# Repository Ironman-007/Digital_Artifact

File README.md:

# Digital_Artifact

Input devices:
- mouse encoder: https://www.amazon.com/gp/product/B0CF9FS3QS/ref=ppx_yo_dt_b_asin_title_o00_s00?ie=UTF8&psc=1
- thumb joystick: https://www.adafruit.com/product/5628
- thumbwheel:
  - https://www.mouser.com/ProductDetail/688-SLLB510100
  - https://www.digikey.com/en/products/detail/alps-alpine/RK10J11R0A0L/21721634?_gl=1*ibrmm*_up*MQ..&gclid=CjwKCAjwvIWzBhAlEiwAHHWgvW0KJP7YJKtc8Nkp65_yvyd6hXw_fZWHygCL2rq1JPE7rxjxQ-IDzBoCs5MQAvD_BwE
- switch: https://www.amazon.com/TWTADE-Momentary-Assortment-Latching-QC-6X6MM/dp/B0858XRGYW/ref=sr_1_1_sspa?crid=2G949J8CR9FFL&dib=eyJ2IjoiMSJ9.kLP3myFYEu7YxaxVJFxt0CR7cWAJtdNJurHc0SBF_I0Rnps__aZ0KqfE4xTtx1MC42MvBkPqKHbfML0_veETEkCh2VtVrYn88wwgkNA-9Elocw1Sk3cp6kjohcve9LoceMxmj3VmeW1gmaoNqY4txQSBajDX9QftLhwdBde_QJkDxFte7JVvVia5f__PGqh0Lh0pOEfo_RKa8_AL1vu4oqmdkYQ97DKHsVdOGzsnvqA.uAgLgaC6A2uq8BuUuJIR0Q7ERczKVlZagGLPBY-yLbA&dib_tag=se&keywords=tactile+switch&qid=1717622919&sprefix=tactile+switch%2Caps%2C122&sr=8-1-spons&sp_csd=d2lkZ2V0TmFtZT1zcF9hdGY&psc=1

MCU:
BC832

IMU:
ICM-20948 (9-DoF)

Actuator:
Linear vibrator

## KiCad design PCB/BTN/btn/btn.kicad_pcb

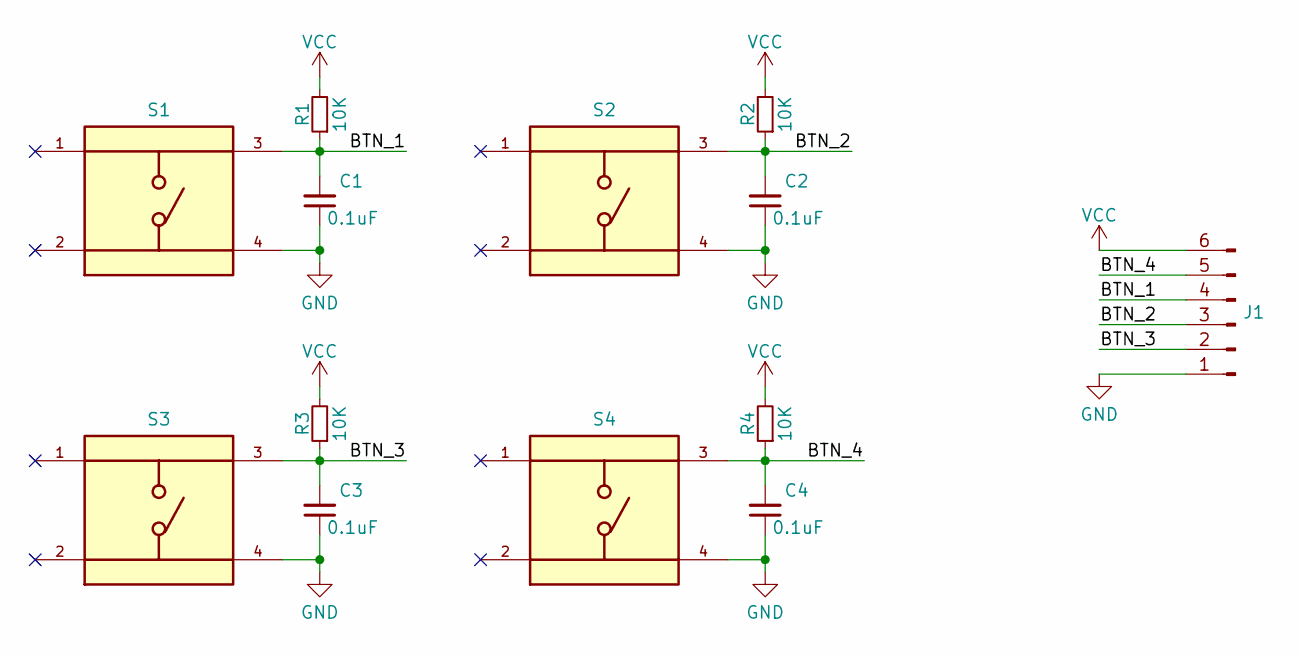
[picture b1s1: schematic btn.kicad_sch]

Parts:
C1, C2, C3, C4: 0.1uF; C_0402_1005Metric_Pad0.74x0.62mm_HandSolder
J1: Conn_01x06_Pin; Pinheader_2mmx6
R1, R2, R3, R4: 10K; R_0402_1005Metric_Pad0.72x0.64mm_HandSolder
S1, S2, S3, S4: TS04-66-95-BK-100-SMT; SW_TS04-66-95-BK-100-SMT; PARTREV 1.0

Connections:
/BTN_1: C1.2, J1.4, R1.1, S1.3
/BTN_2: C2.2, J1.3, R2.1, S2.3
/BTN_3: C3.2, J1.2, R3.1, S3.3
/BTN_4: C4.2, J1.5, R4.1, S4.3
GND: C1.1, C2.1, C3.1, C4.1, J1.1, S1.4, S2.4, S3.4, S4.4
VCC: J1.6, R1.2, R2.2, R3.2, R4.2

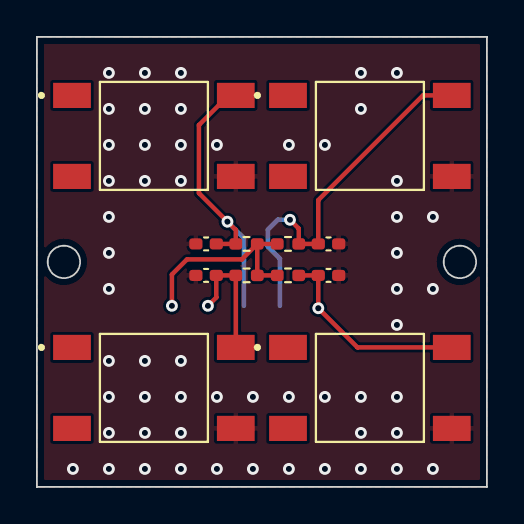
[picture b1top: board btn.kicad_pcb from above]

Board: 2 copper layers, 25.0 x 25.0 mm, 13 parts (1 on the bottom side), 6 nets.

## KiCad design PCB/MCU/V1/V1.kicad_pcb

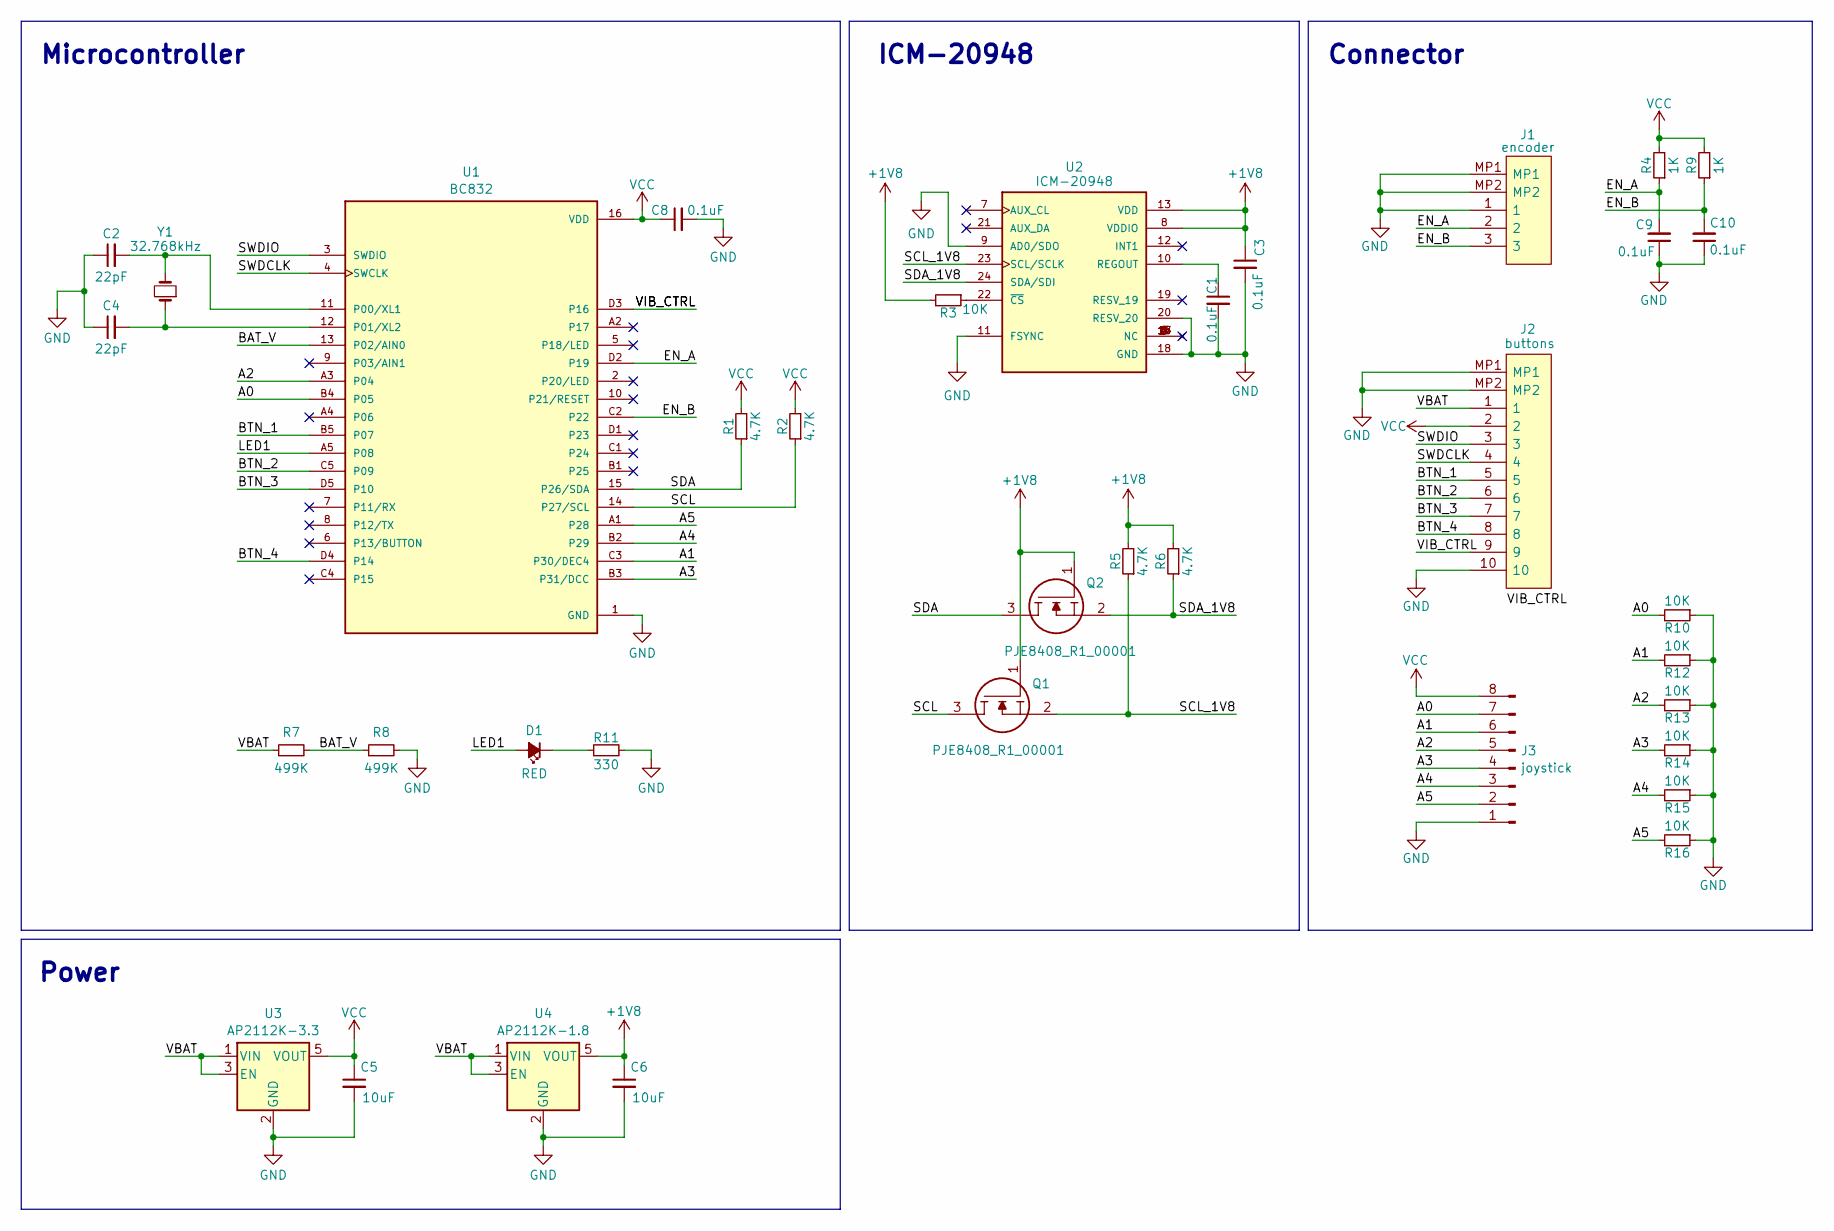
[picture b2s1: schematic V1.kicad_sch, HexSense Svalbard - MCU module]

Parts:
C1, C3, C8, C9, C10: 0.1uF; C_0402_1005Metric_Pad0.74x0.62mm_HandSolder
C2, C4: 22pF; C_0402_1005Metric_Pad0.74x0.62mm_HandSolder
C5, C6: 10uF; C_0402_1005Metric_Pad0.74x0.62mm_HandSolder
D1: RED; LED_0603_1608Metric_Pad1.05x0.95mm_HandSolder
J1: encoder; BM03BSRSSTBTLFSN; Manufacturer_Part_Number BM03B-SRSS-TBT(LF)(SN); Mouser Part Number N/A
J2: buttons; BM10BSRSSTBLFSN; Manufacturer_Part_Number BM10B-SRSS-TB (LF)(SN)
J3: joystick; pinheader_pitch_2mmx8
Q1, Q2: PJE8408_R1_00001; SOTFL50P160X60-3N; Manufacturer_Part_Number PJE8408_R1_00001; Mouser Part Number 241-PJE8408_R1_00001
R1, R2, R5, R6: 4.7K; R_0402_1005Metric_Pad0.72x0.64mm_HandSolder
R3, R10, R12, R13, R14, R15, R16: 10K; R_0402_1005Metric_Pad0.72x0.64mm_HandSolder
R4, R9: 1K; R_0402_1005Metric_Pad0.72x0.64mm_HandSolder
R7, R8: 499K; R_0402_1005Metric_Pad0.72x0.64mm_HandSolder
R11: 330; R_0402_1005Metric_Pad0.72x0.64mm_HandSolder
U1: BC832; XCVR_BC832
U2: ICM-20948; InvenSense_QFN-24_3x3mm_P0.4mm; PARTREV 1.3
U3: AP2112K-3.3; SOT-23-5
U4: AP2112K-1.8; SOT-23-5
Y1: 32.768kHz; C_0805_2012Metric_Pad1.18x1.45mm_HandSolder

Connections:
+1V8: C3.1, C6.1, Q1.1, Q2.1, R3.2, R5.2, R6.2, U2.8 (VDDIO), U2.13 (VDD), U4.5 (VOUT)
/A0: J3.7, R10.2, U1.B4 (P05)
/A1: J3.6, R12.2, U1.C3 (P30/DEC4)
/A2: J3.5, R13.2, U1.A3 (P04)
/A3: J3.4, R14.2, U1.B3 (P31/DCC)
/A4: J3.3, R15.2, U1.B2 (P29)
/A5: J3.2, R16.2, U1.A1 (P28)
/BAT_V: R7.2, R8.1, U1.13 (P02/AIN0)
/BTN_1: J2.5, U1.B5 (P07)
/BTN_2: J2.6, U1.C5 (P09)
/BTN_3: J2.7, U1.D5 (P10)
/BTN_4: J2.8, U1.D4 (P14)
/EN_A: C9.2, J1.2, R4.1, U1.D2 (P19)
/EN_B: C10.2, J1.3, R9.1, U1.C2 (P22)
/LED1: D1.2 (A), U1.A5 (P08)
/SCL: Q1.3, R2.1, U1.14 (P27/SCL)
/SCL_1V8: Q1.2, R5.1, U2.23 (SCL/SCLK)
/SDA: Q2.3, R1.1, U1.15 (P26/SDA)
/SDA_1V8: Q2.2, R6.1, U2.24 (SDA/SDI)
/SWDCLK: J2.4, U1.4 (SWCLK)
/SWDIO: J2.3, U1.3 (SWDIO)
/VBAT: J2.1, R7.1, U3.1 (VIN), U3.3 (EN), U4.1 (VIN), U4.3 (EN)
/VIB_CTRL: J2.9, U1.D3 (P16)
GND: C1.2, C2.1, C3.2, C4.1, C5.2, C6.2, C8.2, C9.1, C10.1, J1.1, J1.MP1, J1.MP2, J2.10, J2.MP1, J2.MP2, J3.1, R8.2, R10.1, R11.2, R12.1, R13.1, R14.1, R15.1, R16.1, U1.1 (GND), U2.9 (AD0/SDO), U2.11 (FSYNC), U2.18 (GND), U2.20 (RESV_20), U3.2 (GND), U4.2 (GND)
unnamed: D1.1 (K), R11.1
unnamed: C2.2, U1.11 (P00/XL1), Y1.2
unnamed: C4.2, U1.12 (P01/XL2), Y1.1
unnamed: C1.1, U2.10 (REGOUT)
unnamed: R3.1, U2.22 (~CS)
VCC: C5.1, C8.1, J2.2, J3.8, R1.2, R2.2, R4.2, R9.2, U1.16 (VDD), U3.5 (VOUT)

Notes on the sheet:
Microcontroller
ICM-20948
Power
Connector

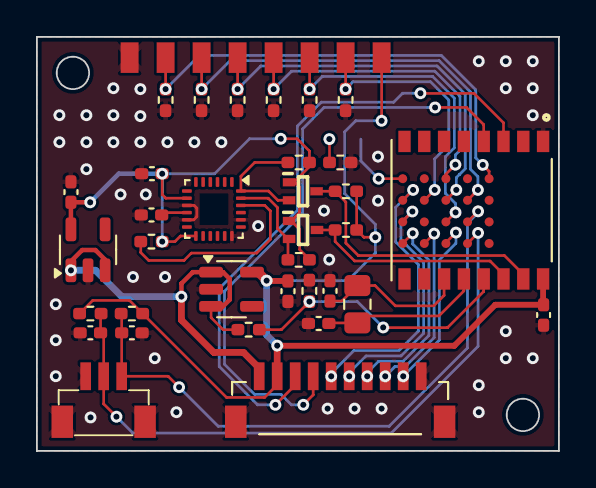
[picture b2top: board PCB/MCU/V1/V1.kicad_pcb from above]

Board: 2 copper layers, 29.0 x 23.0 mm, 36 parts (1 on the bottom side), 30 nets.

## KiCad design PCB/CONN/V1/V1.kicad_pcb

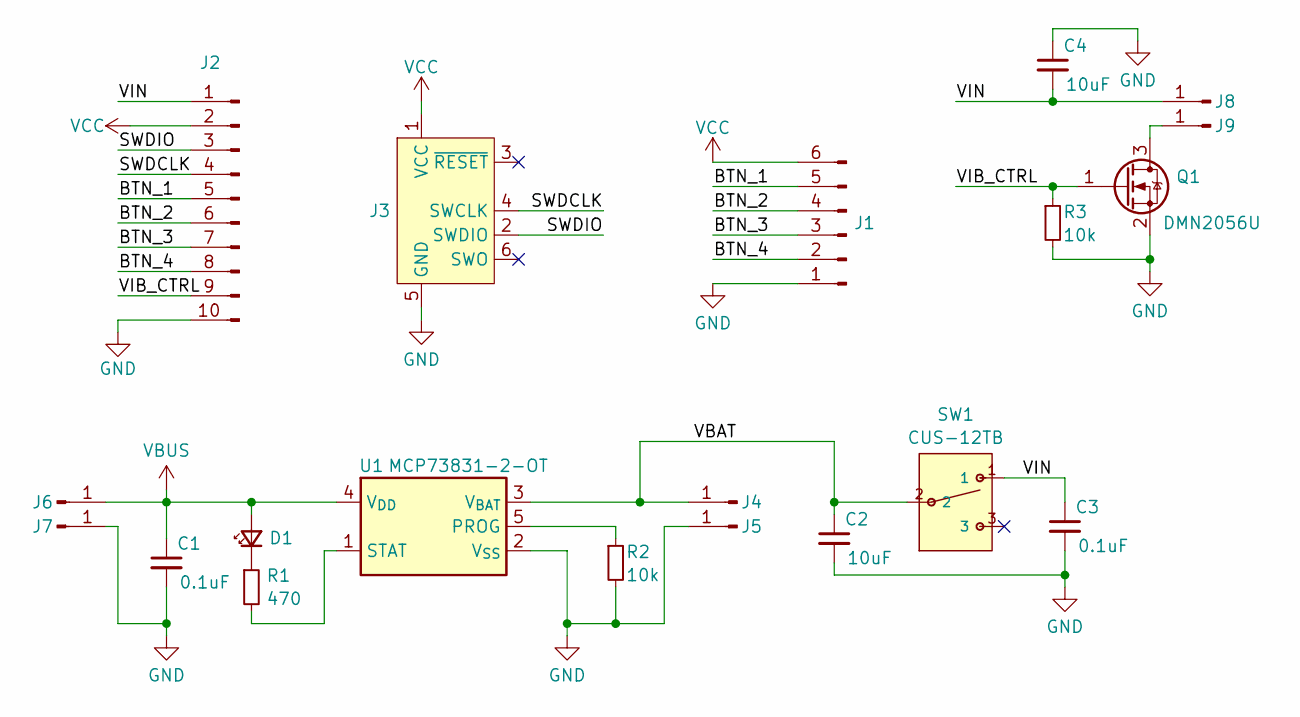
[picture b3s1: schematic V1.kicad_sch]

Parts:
C1, C3: 0.1uF; C_0402_1005Metric_Pad0.74x0.62mm_HandSolder
C2, C4: 10uF; C_0805_2012Metric_Pad1.18x1.45mm_HandSolder
D1: LED_Small; LED_0603_1608Metric_Pad1.05x0.95mm_HandSolder
J1: Conn_01x06_Pin; Pinheader_2mmx6
J2: Conn_01x10_Pin; Pinheader_2mmx10
J3: Conn_ARM_SWD_TagConnect_TC2030-NL; Tag-Connect_TC2030-IDC-NL_2x03_P1.27mm_Vertical
J4, J5, J6, J7, J8, J9: Conn_01x01_Pin; 1_pin
Q1: DMN2056U; SOT-23
R1: 470; R_0402_1005Metric_Pad0.72x0.64mm_HandSolder
R2, R3: 10k; R_0402_1005Metric_Pad0.72x0.64mm_HandSolder
SW1: CUS-12TB; CUS-12B; MANUFACTURER_PART_NUMBER CUS-12TB
U1: MCP73831-2-OT; SOT-23-5

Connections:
/BTN_1: J1.5, J2.5
/BTN_2: J1.4, J2.6
/BTN_3: J1.3, J2.7
/BTN_4: J1.2, J2.8
/SWDCLK: J2.4, J3.4 (SWCLK)
/SWDIO: J2.3, J3.2 (SWDIO)
/VBAT: C2.1, J4.1, SW1.2, U1.3 (V_{BAT})
/VIB_CTRL: J2.9, Q1.1 (G), R3.1
/VIN: C3.1, C4.2, J2.1, J8.1, SW1.1
GND: C1.2, C2.2, C3.2, C4.1, J1.1, J2.10, J3.5 (GND), J5.1, J7.1, Q1.2 (S), R2.2, R3.2, U1.2 (V_{SS})
unnamed: D1.1 (K), R1.1
unnamed: J9.1, Q1.3 (D)
unnamed: R2.1, U1.5 (PROG)
unnamed: R1.2, U1.1 (STAT)
VBUS: C1.1, D1.2 (A), J6.1, U1.4 (V_{DD})
VCC: J1.6, J2.2, J3.1 (VCC)

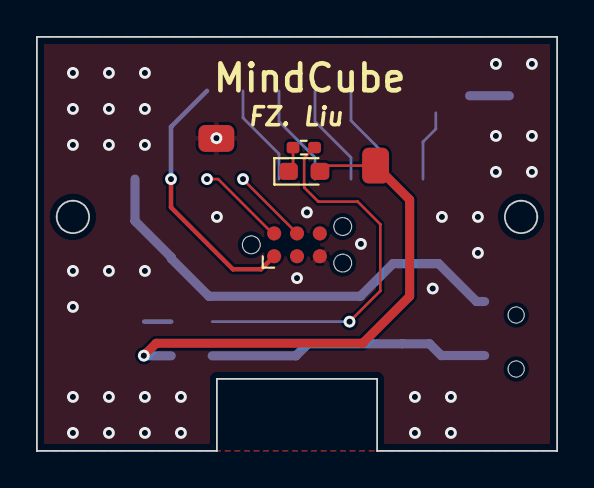
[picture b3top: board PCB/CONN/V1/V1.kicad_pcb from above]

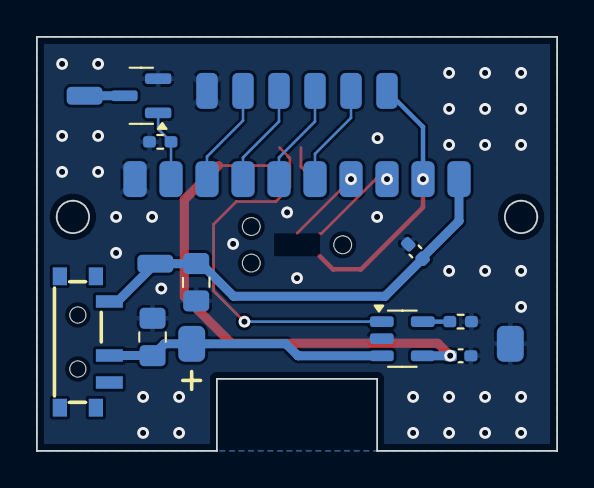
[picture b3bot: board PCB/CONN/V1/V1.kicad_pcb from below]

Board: 2 copper layers, 28.9 x 23.0 mm, 20 parts (15 on the bottom side), 16 nets.

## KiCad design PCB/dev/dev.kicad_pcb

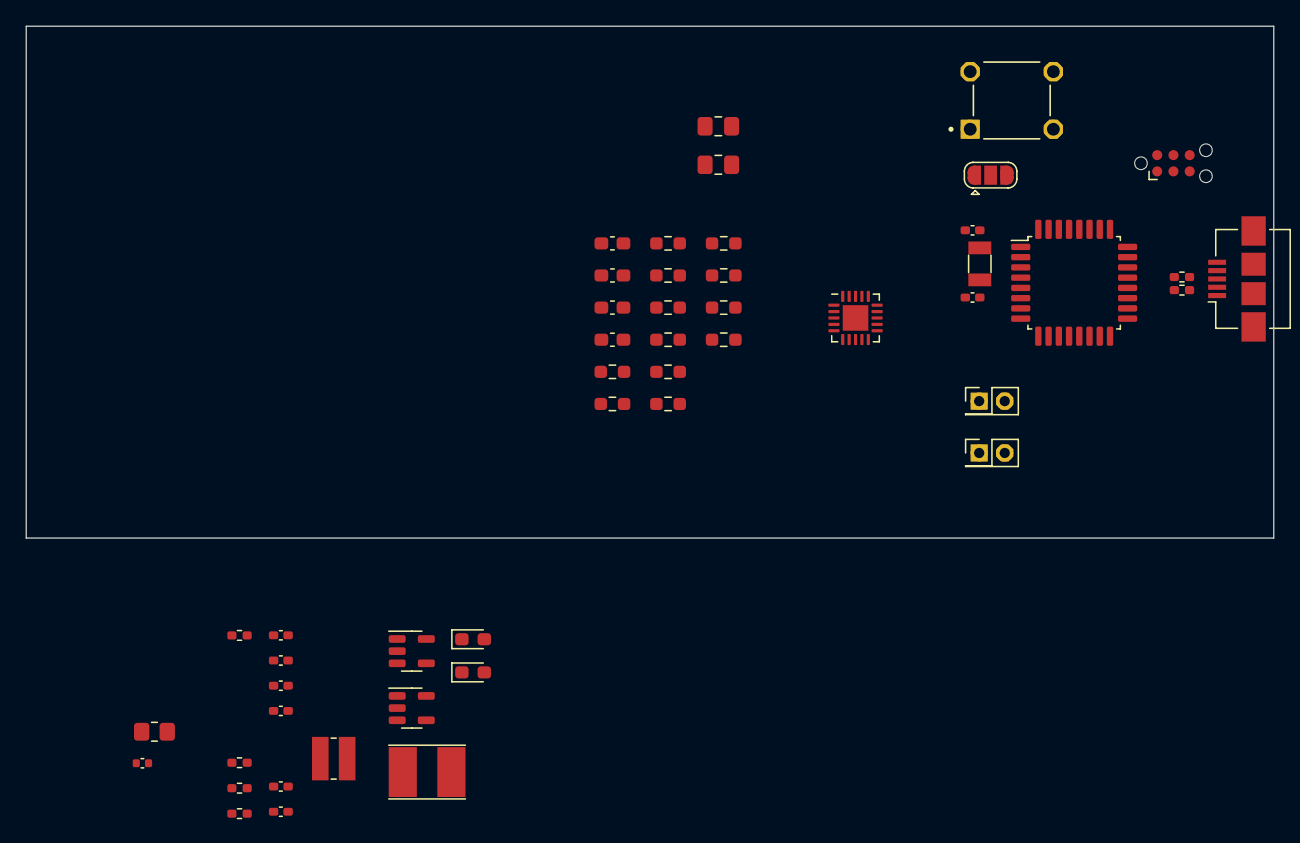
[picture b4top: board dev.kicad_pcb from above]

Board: 2 copper layers, 97.5 x 40.0 mm, 49 parts (0 on the bottom side), 35 nets, no tracks yet.

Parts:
C1, C7, C9, C12, C14: 0.1uF; C_0402_1005Metric_Pad0.74x0.62mm_HandSolder
C2, C3: 4.7uF; C_0603_1608Metric_Pad1.08x0.95mm_HandSolder
C4: 22uF; C_0805_2012Metric_Pad1.18x1.45mm_HandSolder
C5, C8: 10uF; C_0603_1608Metric_Pad1.08x0.95mm_HandSolder
C6: 0.01uF; C_0402_1005Metric_Pad0.74x0.62mm_HandSolder
C10, C11: 18pF; C_0402_1005Metric_Pad0.74x0.62mm_HandSolder
C13: 10pF; C_0402_1005Metric
C15: 47uF; C_0805_2012Metric_Pad1.18x1.45mm_HandSolder
D1, D2: RED; LED_0603_1608Metric_Pad1.05x0.95mm_HandSolder
J2: Battery; PinHeader_2x01_P2.00mm_Vertical
J3: Solar cell; PinHeader_2x01_P2.00mm_Vertical
J4: Conn_ARM_SWD_TagConnect_TC2030-NL; Tag-Connect_TC2030-IDC-NL_2x03_P1.27mm_Vertical
J6: USB_B_Micro; USB_Micro-B_Amphenol_10104110_Horizontal
JP1: BOOT; SolderJumper-3_P1.3mm_Open_RoundedPad1.0x1.5mm
L1: 4.7uH; L_Wuerth_MAPI-3015
L2: 22uH; L_Taiyo-Yuden_NR-40xx_HandSoldering
R1: 7.32M; R_0603_1608Metric_Pad0.98x0.95mm_HandSolder
R2: 330K; R_0603_1608Metric_Pad0.98x0.95mm_HandSolder
R3: 8.25M; R_0603_1608Metric_Pad0.98x0.95mm_HandSolder
R4: 5.62M; R_0603_1608Metric_Pad0.98x0.95mm_HandSolder
R5: 8.45M; R_0603_1608Metric_Pad0.98x0.95mm_HandSolder
R6: 4.75M; R_0603_1608Metric_Pad0.98x0.95mm_HandSolder
R7, R8, R10: 10k; R_0603_1608Metric_Pad0.98x0.95mm_HandSolder
R9: 4.22M; R_0603_1608Metric_Pad0.98x0.95mm_HandSolder
R11, R18: 100; R_0603_1608Metric_Pad0.98x0.95mm_HandSolder
R12: PH; R_0805_2012Metric_Pad1.20x1.40mm_HandSolder
R13: 330; R_0402_1005Metric_Pad0.72x0.64mm_HandSolder
R16, R17: 27; R_0402_1005Metric_Pad0.72x0.64mm_HandSolder
R19: 10K; R_0402_1005Metric_Pad0.72x0.64mm_HandSolder
R20, R21: 100K; R_0402_1005Metric_Pad0.72x0.64mm_HandSolder
S1: TL1105F160Q; SW_TL1105F160Q
U1: BQ25570; QFN-20-1EP_3.5x3.5mm_P0.5mm_EP2x2mm
U2: MCP73831-2-OT; SOT-23-5
U3: STM32L412KBTx; LQFP-32_7x7mm_P0.8mm
U4: ADP160AUJZ-3.3-R7; TSOT-23-5
Y1: 32KHz; Crystal_SMD_3215-2Pin_3.2x1.5mm

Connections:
+5V: C7.1, C15.1, D1.2 (A), J6.1 (VBUS), U2.4 (VDD)
/BAT_V_SENS: R20.2, R21.1, U3.8 (PA2)
/BOOT0: JP1.2 (C), U3.31 (PH3)
/LED: D2.2 (A), U3.27 (PB4)
/SC: C5.1, J3.1, L2.1, U1.2 (VIN_DC)
/SWCLK: J4.4 (SWCLK), U3.24 (PA14)
/SWDIO: J4.2 (SWDIO), U3.23 (PA13)
/USB+: R16.1, U3.22 (PA12)
/USB-: R17.1, U3.21 (PA11)
/VBAT: C3.1, C9.1, J2.1, R20.1, U1.18 (VBAT), U2.3 (VBAT), U4.1 (VIN), U4.3 (EN)
/VOUT_EN: R7.2, U1.6 (VOUT_EN)
/~EN: R8.2, U1.5 (~EN)
/~RST: C13.1, R13.2, U3.4 (NRST)
GND: C1.2, C2.2, C3.2, C4.2, C5.2, C6.2, C7.2, C8.1, C9.2, C10.1, C11.1, C12.2, C13.2, C14.2, C15.2, J2.2, J3.2, J4.5 (GND), J6.5 (GND), J6.6 (Shield), R4.1, R6.1, R7.1, R8.1, R9.1, R10.1, R18.1, R19.1, R21.2, S1.1, U1.1 (VSS), U1.9 (VSS), U1.15 (VSS), U1.17 (VSS), U1.21 (VSS), U2.2 (VSS), U3.16 (VSS), U3.32 (VSS), U4.2 (GND)
unnamed: D1.1 (K), R11.2
unnamed: D2.1 (K), R18.2
unnamed: J6.3 (D+), R16.2
unnamed: J6.2 (D-), R17.2
unnamed: JP1.1 (A), R19.2
unnamed: R13.1, S1.3
unnamed: L2.2, U1.20 (LBOOST)
unnamed: L1.1, U1.16 (LBUCK)
unnamed: R2.1, R5.2, U1.10 (OK_HYST)
unnamed: R5.1, R9.2, U1.11 (OK_PROG)
unnamed: R1.1, R4.2, U1.7 (VBAT_OV)
unnamed: C1.1, C2.1, U1.3 (VOC_SAMP), U1.19 (VSTOR)
unnamed: C4.1, L1.2, U1.14 (VOUT)
unnamed: R3.1, R6.2, U1.12 (VOUT_SET)
unnamed: R1.2, R2.2, R3.2, U1.8 (VRDIV)
unnamed: C6.1, U1.4 (VREF_SAMP)
unnamed: R10.2, U2.5 (PROG)
unnamed: R11.1, U2.1 (STAT)
unnamed: C10.2, R12.2, U3.2 (PC14), Y1.2
unnamed: C11.2, R12.1, U3.3 (PC15), Y1.1
VCC: C8.2, C12.1, C14.1, J4.1 (VCC), U3.1 (VDD), U3.5 (VDDA), U3.17 (VDD), U4.5 (VOUT)

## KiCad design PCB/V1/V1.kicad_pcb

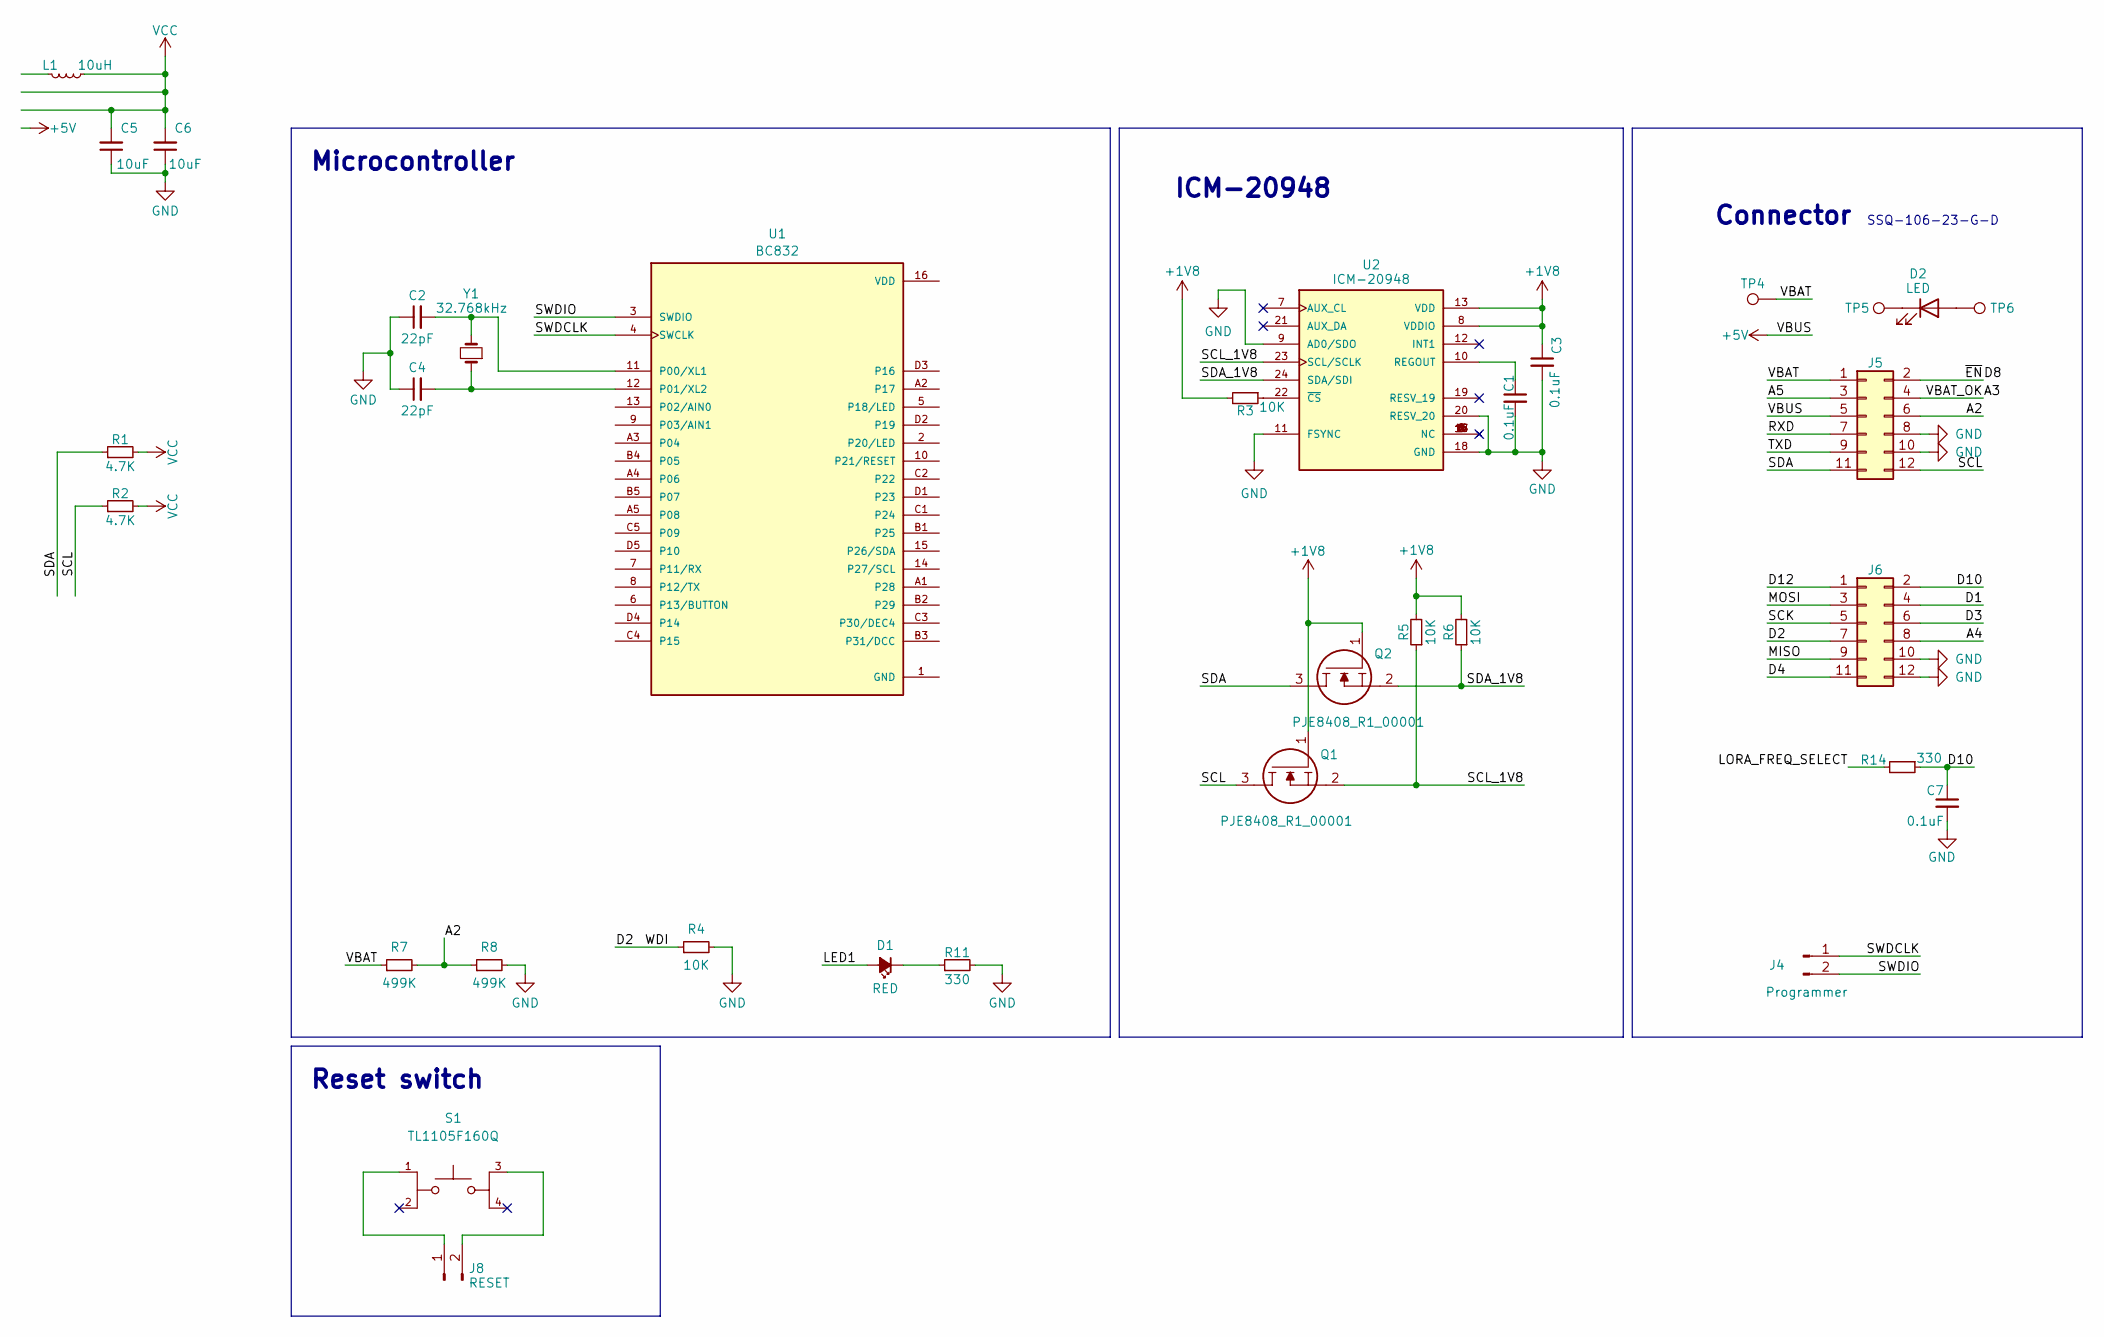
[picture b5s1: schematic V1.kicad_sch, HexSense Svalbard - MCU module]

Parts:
C1, C3, C7: 0.1uF; C_0402_1005Metric_Pad0.74x0.62mm_HandSolder
C2, C4: 22pF; C_0402_1005Metric_Pad0.74x0.62mm_HandSolder
C5, C6: 10uF; C_0402_1005Metric_Pad0.74x0.62mm_HandSolder
D1: RED; LED_0603_1608Metric_Pad1.05x0.95mm_HandSolder
D2: LED; D_0603_1608Metric_Pad1.05x0.95mm_HandSolder
J4: Programmer; PinHeader_1x02_P2.54mm_Vertical
J5, J6: Conn_02x06_Odd_Even; PinHeader_2x06_P2.54mm_Vertical
J8: RESET; PinHeader_1x02_P2.00mm_Vertical
L1: 10uH; L_0603_1608Metric_Pad1.05x0.95mm_HandSolder
Q1, Q2: PJE8408_R1_00001; SOTFL50P160X60-3N; Manufacturer_Part_Number PJE8408_R1_00001; Mouser Part Number 241-PJE8408_R1_00001
R1, R2: 4.7K; R_0402_1005Metric_Pad0.72x0.64mm_HandSolder
R3, R5, R6: 10K; R_0402_1005Metric_Pad0.72x0.64mm_HandSolder
R4: 10K; R_0402_1005Metric
R7, R8: 499K; R_0402_1005Metric_Pad0.72x0.64mm_HandSolder
R11, R14: 330; R_0402_1005Metric_Pad0.72x0.64mm_HandSolder
S1: TL1105F160Q; SW_TL1105F160Q; PARTREV A
TP4, TP5, TP6: TestPoint; TestPoint_Pad_1.5x1.5mm
U1: BC832; XCVR_BC832
U2: ICM-20948; InvenSense_QFN-24_3x3mm_P0.4mm; PARTREV 1.3
Y1: 32.768kHz; C_0805_2012Metric_Pad1.18x1.45mm_HandSolder

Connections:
+1V8: C3.1, Q1.1, Q2.1, R3.2, R5.2, R6.2, U2.8 (VDDIO), U2.13 (VDD)
+5V: J5.5
/A2: J5.6, R7.2, R8.1
/A3: J5.4
/A4: J6.8
/A5: J5.3
/D1: J6.4
/D2: J6.7, R4.1
/D3: J6.6
/D4: J6.11
/D8: J5.2
/D10: C7.1, J6.2, R14.1
/D12: J6.1
/LED1: D1.2 (A)
/LORA_FREQ_SELECT: R14.2
/MISO: J6.9
/MOSI: J6.3
/RXD: J5.7
/SCK: J6.5
/SCL: J5.12, Q1.3, R2.1
/SCL_1V8: Q1.2, R5.1, U2.23 (SCL/SCLK)
/SDA: J5.11, Q2.3, R1.1
/SDA_1V8: Q2.2, R6.1, U2.24 (SDA/SDI)
/SWDCLK: J4.1, U1.4 (SWCLK)
/SWDIO: J4.2, U1.3 (SWDIO)
/TXD: J5.9
/VBAT: J5.1, R7.1, TP4.1
GND: C1.2, C2.1, C3.2, C4.1, C5.1, C6.1, C7.2, J5.8, J5.10, J6.10, J6.12, R4.2, R8.2, R11.2, U2.9 (AD0/SDO), U2.11 (FSYNC), U2.18 (GND), U2.20 (RESV_20)
unnamed: D1.1 (K), R11.1
unnamed: D2.2 (A), TP6.1
unnamed: D2.1 (K), TP5.1
unnamed: J8.1, S1.1
unnamed: J8.2, S1.3
unnamed: C2.2, U1.11 (P00/XL1), Y1.2
unnamed: C4.2, U1.12 (P01/XL2), Y1.1
unnamed: C1.1, U2.10 (REGOUT)
unnamed: R3.1, U2.22 (~CS)
VCC: C5.2, C6.2, L1.1, R1.2, R2.2

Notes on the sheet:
Microcontroller
Reset switch
ICM-20948
Connector
SSQ-106-23-G-D

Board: 2 copper layers, 30 parts (0 on the bottom side), 20 nets, no tracks yet.

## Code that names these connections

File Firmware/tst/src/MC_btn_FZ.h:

#pragma once

#include <Arduino.h>

#define BTN_1_PIN 7
#define BTN_2_PIN 9
#define BTN_3_PIN 10
#define BTN_4_PIN 14

extern uint8_t btn1;
extern uint8_t btn2;
extern uint8_t btn3;
extern uint8_t btn4;

extern void MC_btnInit(void);
extern void MC_read_btn(void);

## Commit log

2024-04-08 udated by FZ
2024-07-14 blink LED working
2024-07-14 Joystick working
2024-07-17 BLE sends data workign
2024-07-17 BLE all except encoder working
2024-07-17 added encoder but seems not working yet
2024-07-18 Encoder seems working but only one direction
2024-07-18 Encoder seems working now, lower the sample rate to 200Hz
2024-08-08 UIST demo paper
2024-08-22 cobs and GUI all working
